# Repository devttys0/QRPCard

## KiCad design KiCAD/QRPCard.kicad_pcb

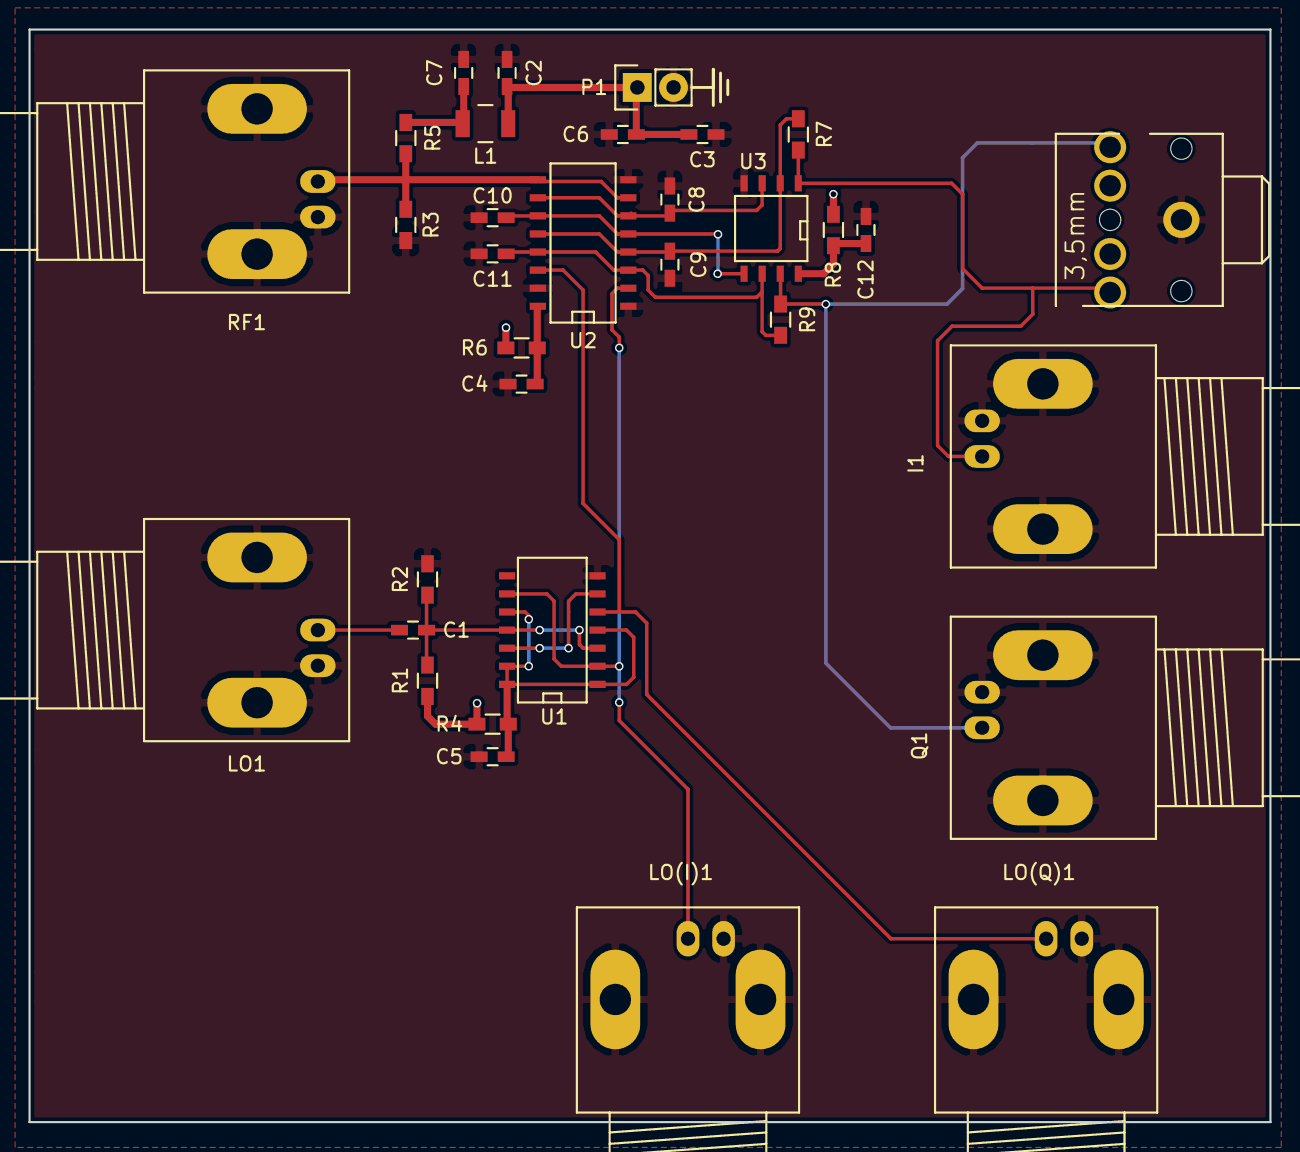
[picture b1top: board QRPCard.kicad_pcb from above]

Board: 2 copper layers, 87.1 x 76.7 mm, 33 parts (0 on the bottom side), 18 nets.

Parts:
C1, C4, C5, C8, C9, C10, C11, C12: 0.1uF; C_0603_HandSoldering
C2, C3, C7: 0.01uF; C_0603_HandSoldering
C6: 10uF; C_0603_HandSoldering
I1: BNC; BNC_Socket_TYCO-AMP_LargePads
J1: STX-3100-5N; STX3100
L1: 470uH; Neosid_Inductor_SM-NE30_SMD1210
LO1: BNC; BNC_Socket_TYCO-AMP_LargePads
LO(I)1: BNC; BNC_Socket_TYCO-AMP_LargePads
LO(Q)1: BNC; BNC_Socket_TYCO-AMP_LargePads
P1: +5v; Pin_Header_Straight_1x02
Q1: BNC; BNC_Socket_TYCO-AMP_LargePads
R1: 560k; R_0603_HandSoldering
R2: 220k; R_0603_HandSoldering
R3, R4, R5, R6, R8: 100; R_0603_HandSoldering
R7, R9: 100k; R_0603_HandSoldering
RF1: BNC; BNC_Socket_TYCO-AMP_LargePads
U1: SN74HC74; SOIC-14_N
U2: FST3253; SO-16-N
U3: TSV992A; SOIC-8-N

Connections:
+5V: C2.2, C3.2, C6.2, L1.1, P1.1, R1.1, R4.1, R6.1, R8.1
GND: C2.1, C3.1, C4.1, C5.2, C6.1, C7.1, C8.1, C9.1, C10.1, C11.1, C12.1, I1.2, J1.1, LO1.2, LO(I)1.2, LO(Q)1.2, P1.2, Q1.2, R2.2, R3.1, RF1.2, U1.7, U2.1, U2.8, U2.15, U3.4
unnamed: C1.1, R1.2, R2.1, U1.3, U1.11
unnamed: C1.2, LO1.1
unnamed: C4.2, R6.2, U2.16
unnamed: C5.1, R4.2, U1.1, U1.4, U1.10, U1.13, U1.14
unnamed: C7.2, L1.2, R5.1
unnamed: C8.2, U2.6, U2.10, U3.3
unnamed: C9.2, R7.2, U2.4, U2.12, U3.2
unnamed: C10.2, U2.5, U2.11, U3.5
unnamed: C11.2, R9.2, U2.3, U2.13, U3.6
unnamed: C12.2, R8.2, U3.8
unnamed: I1.1, J1.2, R7.1, U3.1
unnamed: J1.5, Q1.1, R9.1, U3.7
unnamed: LO(I)1.1, U1.2, U1.9, U2.2
unnamed: LO(Q)1.1, U1.5, U2.14
unnamed: R3.2, R5.2, RF1.1, U2.7, U2.9
unnamed: U1.6, U1.12

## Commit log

2016-08-31 Initial commit of test/dev board
2016-08-31 Gerber check in
